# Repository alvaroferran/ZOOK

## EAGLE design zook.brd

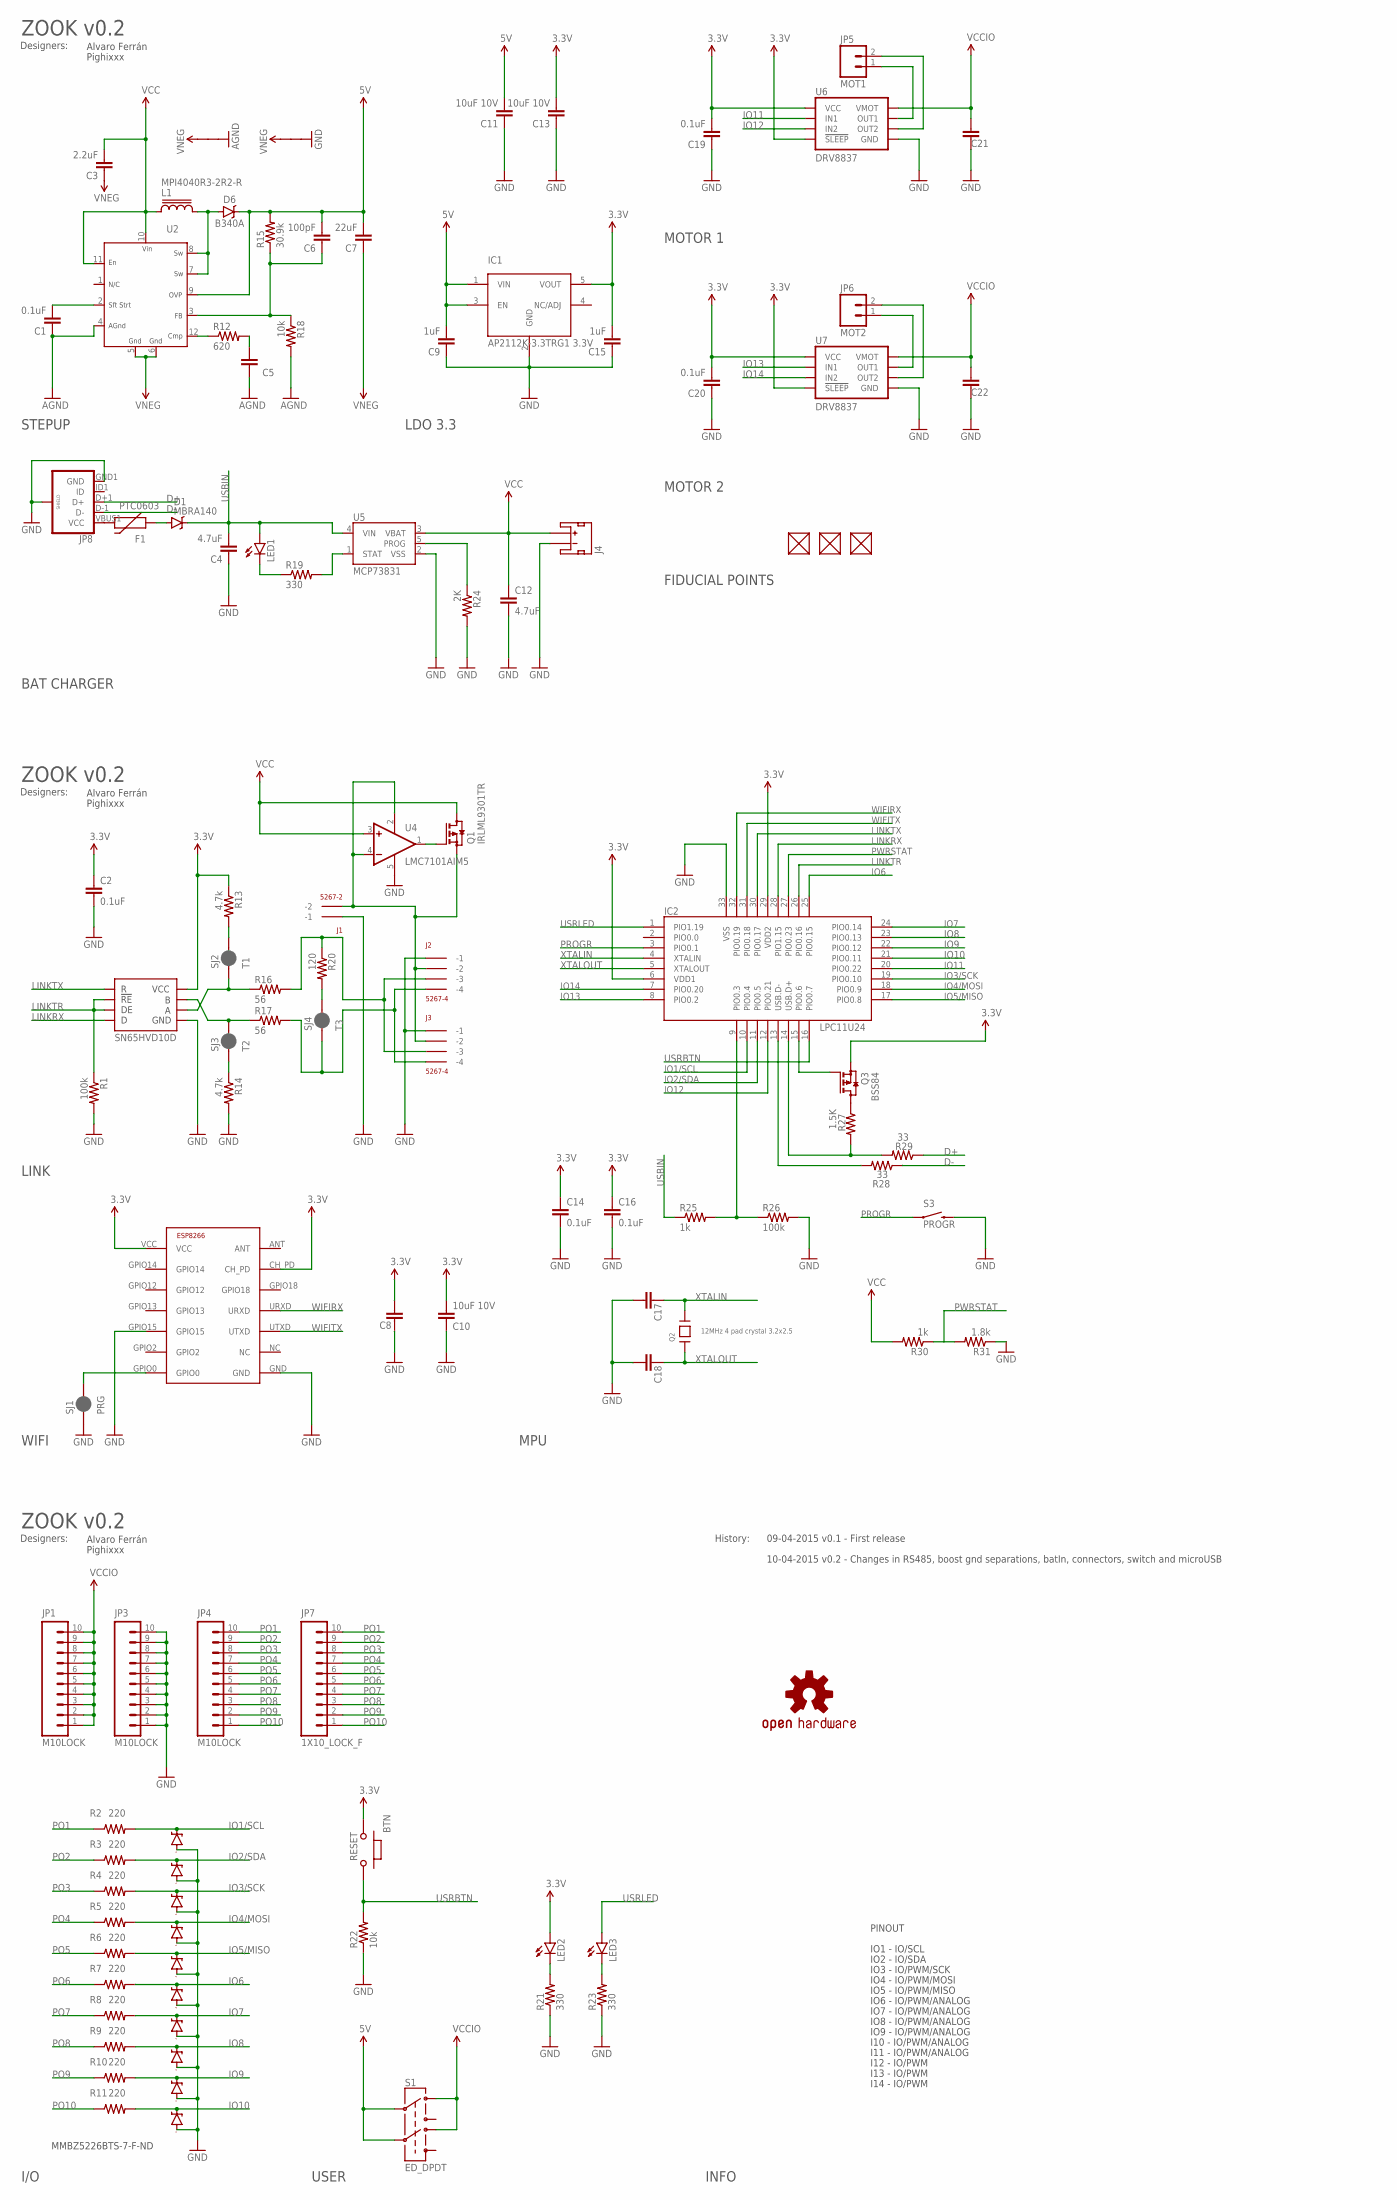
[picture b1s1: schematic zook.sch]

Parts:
BTN: RESET; 157SW
C1, C2, C8, C14, C16, C19, C20, C21, C22: 0.1uF; 0402-CAP
C3: 2.2uF; 0402-CAP
C4, C12: 4.7uF; 0402-CAP
C5: 10nF; 0402-CAP
C6: 100pF; 0402-CAP
C7: 22uF; 0805
C9, C15: 1uF; 0402-CAP
C10, C11, C13: 10uF 10V; 0402-CAP
C17, C18: 27pF; 0402-CAP
D1: MBRA140; SMA-DIODE
D2, D3, D4, D5: ZENERARRAY; SOT363
D6: B340A; SMA-DIODE
F1: PTC0603; 0603
FUD1, FUD2, FUD3: FIDUCIAL; FIDUCIAL_40MIL
GND5, GND6: VIRTUAL_GND; STARGND
IC1: AP2112K-3.3TRG1 3.3V; SOT23-5
IC2: LPC11U24; HVQFN33_5X5MM
J1: 5267-2
J2, J3: 5267-4
J4: BATT; JST-2-SMD
JP1, JP3, JP4: M10LOCK; 1X10_LOCK
JP5: MOT1; MOLEX-1X2
JP6: MOT2; MOLEX-1X2
JP7: 1X10_LOCK_F
JP8: USB_MICROB_PLUGCONN-11752; USB-B-MICRO-SMD_V03
L1: MPI4040R3-2R2-R
LED1, LED2, LED3: LED0603; LED-0603
LOGO3: OSHW-LOGOS; OSHW-LOGO-S
Q1: IRLML9301TR; SOT23
Q2: 12MHz 4 pad crystal 3.2x2.5; CRYSTAL_3.2X2.5
Q3: BSS84; SOT23
R1, R26: 100k; 0402-RES
R2, R3, R4, R5, R6, R7, R8, R9, R10, R11: 220; 0603-RES
R12: 620; 0402-RES
R13, R14: 4.7k; 0402-RES
R15: 30.9k; 0402-RES
R16, R17: 56; 0402-RES
R18, R22: 10k; 0402-RES
R19, R21, R23: 330; 0402-RES
R20: 120; 0402-RES
R24: 2K; 0402-RES
R25, R30: 1k; 0402-RES
R27: 1.5K; 0402-RES
R28, R29: 33; 0402-RES
R31: 1.8k; 0402-RES
S1: ED_DPDT
S3: PROGR; TACTILE-PTH-SIDEEZ
SJ1: PRG; PAD-JUMPER-2-NC_BY_PASTE_YES_SILK
SJ2: T1; PAD-JUMPER-2-NC_BY_PASTE_YES_SILK
SJ3: T2; PAD-JUMPER-2-NC_BY_PASTE_YES_SILK
SJ4: T3; PAD-JUMPER-2-NC_BY_PASTE_YES_SILK
U2: MIC2253; MLF12_3.0MM_X_3.0MM
U3: ESP8266; ESP-03
U4: LMC7101AIM5; SOT23-5
U5: MCP73831; SOT23-5
U6, U7: DRV8837; DSG
U8: SN65HVD10D; SO08

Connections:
3.3V: BTN.1, C2.1, C8.2, C10.2, C13.2, C14.1, C15.2, C16.1, C19.2, C20.2, IC1.5 (VOUT), IC2.6 (VDD1), IC2.29 (VDD2), LED2.A, Q3.2 (S), R13.1, U3.CH_PD, U3.VCC, U6.7 (!SLEEP), U6.8 (VCC), U7.7 (!SLEEP), U7.8 (VCC), U8.8
5V: C6.2, C7.2, C9.2, C11.2, D6.C, IC1.1 (VIN), IC1.3 (EN), R15.2, S1.2, S1.5, U2.9 (OVP)
AGND: C1.1, C5.1, GND5.P$2, R18.2, U2.4 (AGND)
D+: JP8.D+1 (D+), R29.1
D-: JP8.D-1 (D-), R28.1
GND: C2.2, C4.1, C8.1, C9.1, C10.1, C11.1, C12.2, C13.1, C14.2, C15.1, C16.2, C17.2, C18.2, C19.1, C20.1, C21.1, C22.1, D2.1 (A), D2.2 (A), D2.3 (A), D3.1 (A), D3.2 (A), D3.3 (A), D4.1 (A), D4.2 (A), D4.3 (A), D5.1 (A), GND6.P$2, IC1.2 (GND), IC2.33 (VSS), J1.P$1 (-1), J2.P$1 (-1), J3.P$1 (-1), J4.1 (-), JP3.1, JP3.2, JP3.3, JP3.4, JP3.5, JP3.6, JP3.7, JP3.8, JP3.9, JP3.10, JP8.GND1 (GND), JP8.SHIELD1 (SHIELD), JP8.SHIELD2 (SHIELD), JP8.SHIELD3 (SHIELD), R1.2, R14.2, R21.1, R22.1, R23.1, R24.2, R26.2, R31.1, S3.2, SJ1.1, U3.GND, U3.GPIO15, U4.5 (V-), U5.2 (VSS), U6.4 (GND), U6.PAD (GND), U7.4 (GND), U7.PAD (GND), U8.5
IO1/SCL: D2.6 (C), IC2.10 (PIO0.4), R2.2
IO2/SDA: D2.5 (C), IC2.11 (PIO0.5), R3.2
IO3/SCK: D2.4 (C), IC2.19 (PIO0.10), R4.2
IO4/MOSI: D3.6 (C), IC2.18 (PIO0.9), R5.2
IO5/MISO: D3.5 (C), IC2.17 (PIO0.8), R6.2
IO6: D3.4 (C), IC2.25 (PIO0.15), R7.2
IO7: D4.6 (C), IC2.24 (PIO0.14), R8.2
IO8: D4.5 (C), IC2.23 (PIO0.13), R9.2
IO9: D4.4 (C), IC2.22 (PIO0.12), R10.2
IO10: D5.6 (C), IC2.21 (PIO0.11), R11.2
IO11: IC2.20 (PIO0.22), U6.6 (IN1)
IO12: IC2.12 (PIO0.21), U6.5 (IN2)
IO13: IC2.8 (PIO0.2), U7.6 (IN1)
IO14: IC2.7 (PIO0.20), U7.5 (IN2)
LINKRX: IC2.28 (PIO1.15), U8.4
LINKTR: IC2.26 (PIO0.16), R1.1, U8.2, U8.3
LINKTX: IC2.30 (PIO0.17), U8.1
unnamed: J2.P$4 (-4), J3.P$4 (-4), R17.2, SJ4.1
unnamed: LED2.C, R21.2
unnamed: C5.2, R12.2
unnamed: D6.A, L1.P$2 (2), U2.7 (SW), U2.8 (SW)
unnamed: C1.2, U2.2 (SS)
unnamed: F1.2, JP8.VBUS1 (VCC)
unnamed: R12.1, U2.12 (CMP)
unnamed: D1.A, F1.1
unnamed: JP5.1, U6.2 (OUT1)
unnamed: JP5.2, U6.3 (OUT2)
unnamed: R19.2, U5.1 (STAT)
unnamed: LED1.C, R19.1
unnamed: JP6.1, U7.2 (OUT1)
unnamed: JP6.2, U7.3 (OUT2)
unnamed: R17.1, SJ3.2, U8.7
unnamed: R16.1, SJ2.1, U8.6
unnamed: R13.2, SJ2.2
unnamed: R20.2, SJ4.2
unnamed: R14.1, SJ3.1
unnamed: J2.P$3 (-3), J3.P$3 (-3), R16.2, R20.1
unnamed: LED3.C, R23.2
unnamed: C6.1, R15.1, R18.1, U2.3 (FB)
unnamed: Q1.1 (G), U4.1 (OUT)
unnamed: J1.P$2 (-2), J2.P$2 (-2), J3.P$2 (-2), Q1.2 (S), U4.2 (V+), U4.4 (-IN)
unnamed: IC2.14 (USB.D+), R27.2, R29.2
unnamed: SJ1.2, U3.GPIO0
unnamed: IC2.13 (USB.D-), R28.2
unnamed: Q3.3 (D), R27.1
unnamed: IC2.15 (PIO0.6), Q3.1 (G)
P0.3/ISP_COMMAND_USB_HIGH: IC2.9 (PIO0.3), R25.2, R26.1
PO1: JP4.10, JP7.10, R2.1
PO2: JP4.9, JP7.9, R3.1
PO3: JP4.8, JP7.8, R4.1
PO4: JP4.7, JP7.7, R5.1
PO5: JP4.6, JP7.6, R6.1
PO6: JP4.5, JP7.5, R7.1
PO7: JP4.4, JP7.4, R8.1
PO8: JP4.3, JP7.3, R9.1
PO9: JP4.2, JP7.2, R10.1
PO10: JP4.1, JP7.1, R11.1
PROG: R24.1, U5.5 (PROG)
PROGR: IC2.3 (PIO0.1), S3.1
PWRSTAT: IC2.27 (PIO0.23), R30.1, R31.2
USBIN: C4.2, D1.C, LED1.A, R25.1, U5.4 (VIN)
USRBTN: BTN.2, IC2.16 (PIO0.7), R22.2
USRLED: IC2.1 (PIO1.19), LED3.A
VCC: C3.2, C12.1, J4.2 (+), L1.P$1 (1), Q1.3 (D), R30.2, U2.10 (VIN), U2.11 (EN), U4.3 (+IN), U5.3 (VBAT)
VCCIO: C21.2, C22.2, JP1.1, JP1.2, JP1.3, JP1.4, JP1.5, JP1.6, JP1.7, JP1.8, JP1.9, JP1.10, S1.1, S1.4, U6.1 (VMOT), U7.1 (VMOT)
VNEG: C3.1, C7.1, GND5.P$1, GND6.P$1, U2.5 (GND), U2.6 (GND)
WIFIRX: IC2.32 (PIO0.19), U3.URXD
WIFITX: IC2.31 (PIO0.18), U3.UTXD
XTALIN: C17.1, IC2.4 (XTALIN), Q2.3
XTALOUT: C18.1, IC2.5 (XTALOUT), Q2.1

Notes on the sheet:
STEPUP
LDO 3.3
BAT CHARGER
MOTOR 1
MOTOR 2
FIDUCIAL POINTS
ZOOK v0.2
Designers:
Alvaro Ferrán
Pighixxx
LINK
WIFI
MPU
I/O
USER
INFO
History:
09-04-2015 v0.1 - First release
IO1 - IO/SCL
IO2 - IO/SDA
IO3 - IO/PWM/SCK
IO4 - IO/PWM/MOSI
IO5 - IO/PWM/MISO
IO6 - IO/PWM/ANALOG
IO7 - IO/PWM/ANALOG
IO8 - IO/PWM/ANALOG
IO9 - IO/PWM/ANALOG
I10 - IO/PWM/ANALOG
PINOUT
MMBZ5226BTS-7-F-ND
10-04-2015 v0.2 - Changes in RS485, boost gnd separations, batIn, connectors, switch and microUSB
I11 - IO/PWM/ANALOG
I12 - IO/PWM
I13 - IO/PWM
I14 - IO/PWM

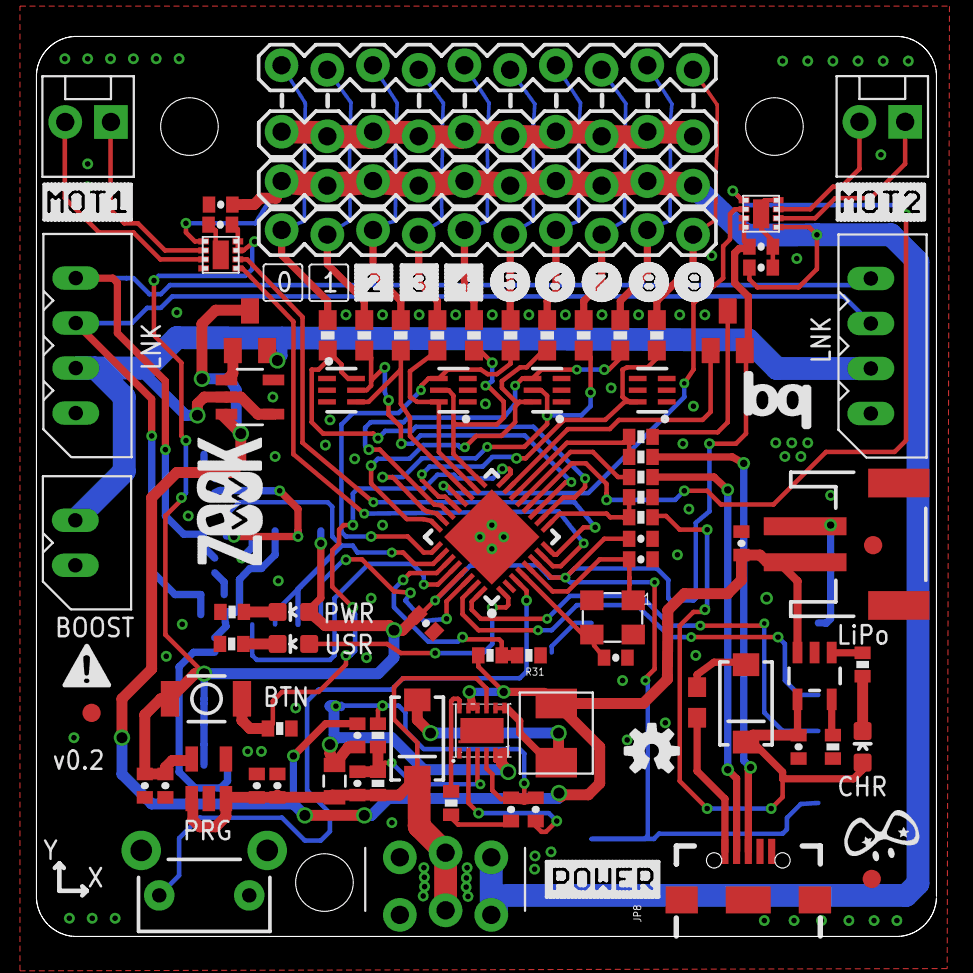
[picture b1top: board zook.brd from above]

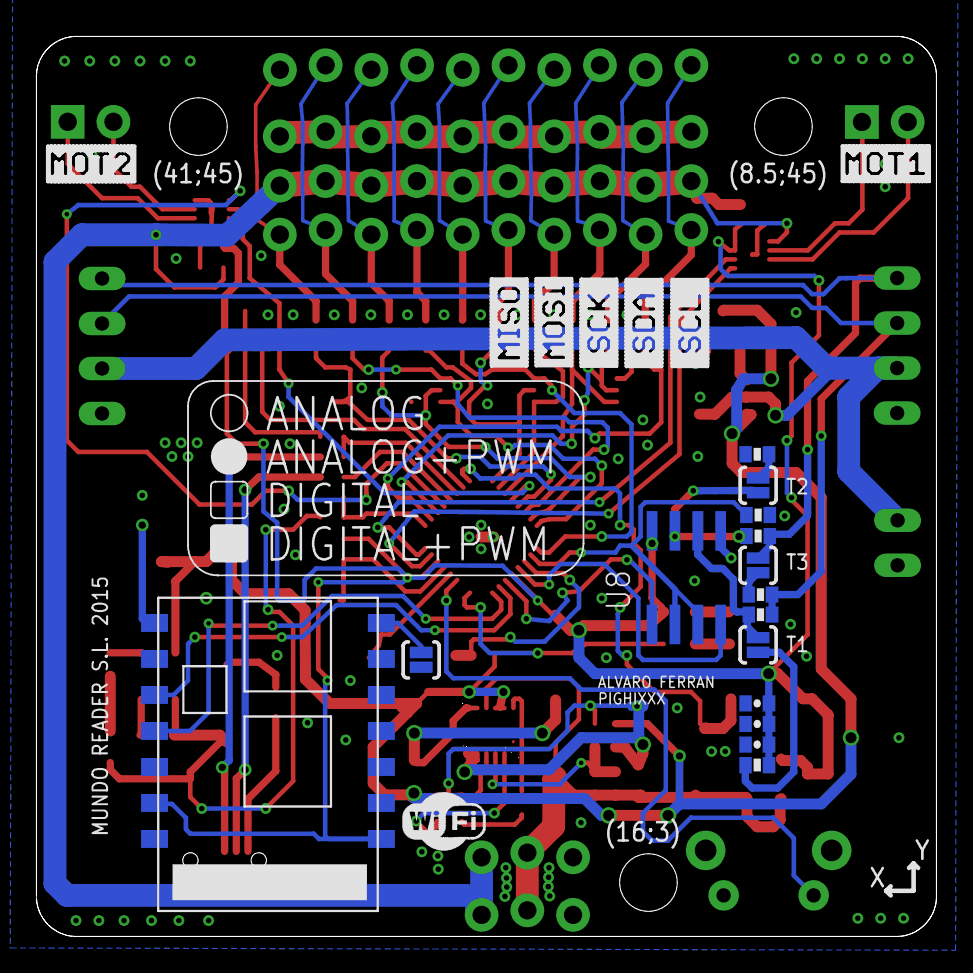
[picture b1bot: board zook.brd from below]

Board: 2 copper layers, 50.0 x 50.0 mm, 126 parts (26 on the bottom side), 76 nets.

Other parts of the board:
U$1: S_1_P
U$2: S_2
U$3: S_0_P
U$4: S_5_R
U$5: S_3
U$6: S_4
U$7: S_6_R
U$8: S_7_R
U$9: S_8_R
U$10: S_9_R
U$11: S_SCL
U$12: S_SDA
U$13: S_MOSI
U$14: S_MISO
U$15: S_SCK
U$16, U$25: S_MOT1
U$17, U$26: S_MOT2
U$18: S_LEGEND
U$19: S_POWER
U$20: S_WIFI
U$21: S_ZOOK_LOGO
U$22: S_ATTENTION
U$23: PIGHIXXX_LOGO
U$27: BQ_LOGO_MEDIUM

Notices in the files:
parts and their libraries:
SparkFun-PowerIC: Licensing: CC v3.0 Share-Alike You are welcome to use this library for commercial purposes.
SparkFun-Connectors: Licensing: Creative Commons ShareAlike 4.0 International - https://creativecommons.org/licenses/by-sa/4.0
